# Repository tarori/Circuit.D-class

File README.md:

Class D amplifier using TPA3118

Not recommended because the sound is not so good

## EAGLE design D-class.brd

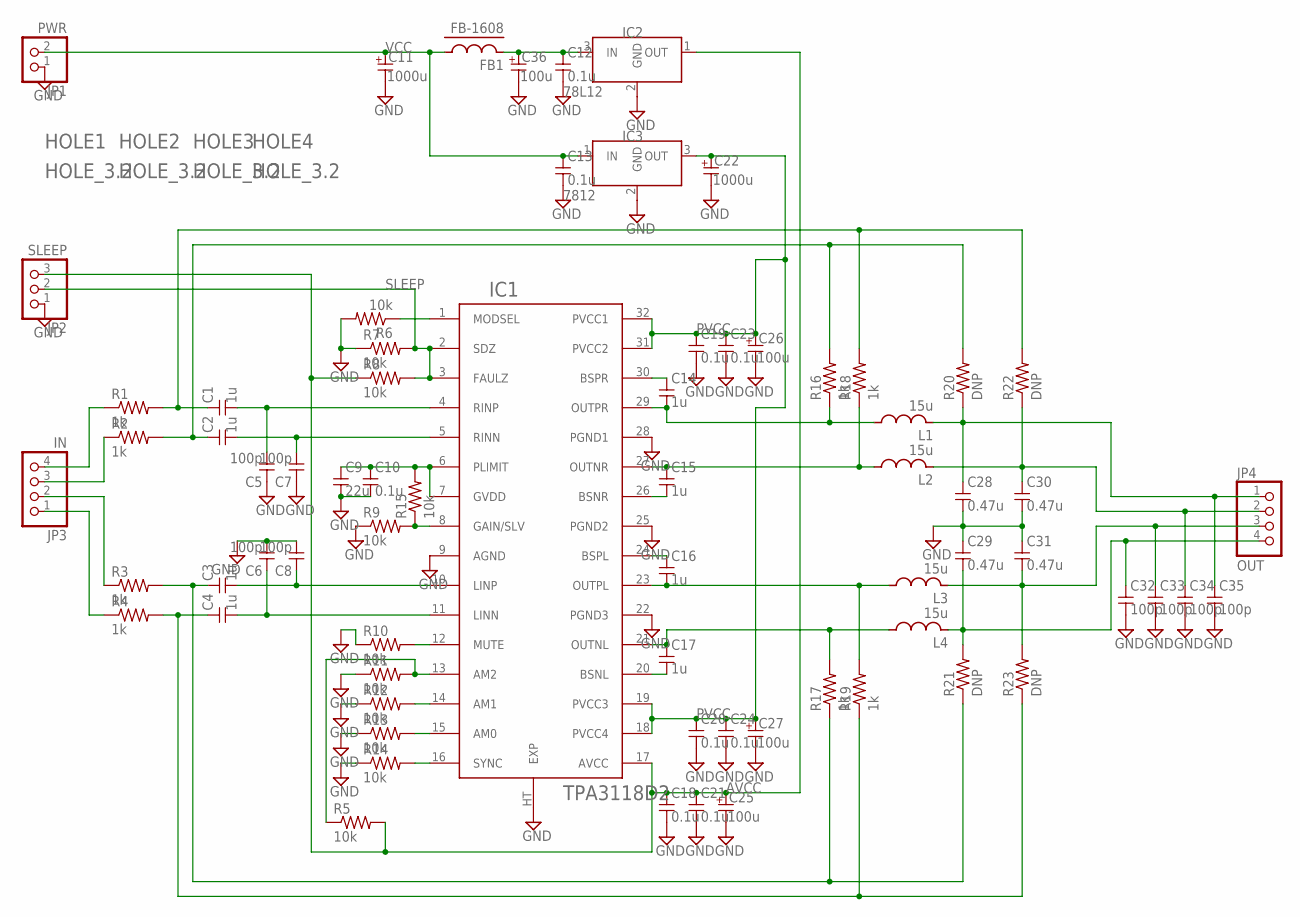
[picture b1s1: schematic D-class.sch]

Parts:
C1, C2, C3, C4: 1u; 3216
C5, C6, C7, C8, C32, C33, C34, C35: 100p; 1608
C9: 22u; 2012
C10, C12, C13, C18, C19, C20: 0.1u; 1608
C11, C22: 1000u; E5-10
C14, C15, C16, C17: 1u; 1608
C21, C23, C24: 0.1u; 2012
C25, C26, C27, C36: 100u; E2.5-6.5
C28, C29, C30, C31: 0.47u; C050-030X075
FB1: FB-1608; 1608
HOLE1, HOLE2, HOLE3, HOLE4: HOLE_3.2
IC1: TPA3118D2; HTSSOP32DAP
IC2: 78L12; TO-92
IC3: 7812; TO-220
JP1: PWR; 1X02
JP2: SLEEP; 1X03
JP3: IN; 1X04
JP4: OUT; 1X04
L1, L2, L3, L4: 15u; L5-7,5
R1, R2, R3, R4, R16, R17, R18, R19: 1k; 0207/2V
R5, R6, R7, R8, R9, R10, R11, R12, R13, R14, R15: 10k; 1608
R20, R21, R22, R23: DNP; 0207/2V

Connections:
AVCC: C18.1, C21.1, C25.+ (1), IC1.17 (AVCC), IC2.1 (OUT), JP2.3, R5.2, R8.1
GND: C5.1, C6.2, C7.1, C8.2, C9.2, C10.2, C11.- (2), C12.2, C13.2, C18.2, C19.2, C20.2, C21.2, C22.- (2), C23.2, C24.2, C25.- (2), C26.- (2), C27.- (2), C28.2, C29.1, C30.2, C31.1, C32.2, C33.2, C34.2, C35.2, C36.- (2), IC1.9 (AGND), IC1.22 (PGND3), IC1.25 (PGND2), IC1.28 (PGND1), IC1.HT (EXP), IC2.2 (GND), IC3.2 (GND), JP1.1, JP2.1, R6.2, R7.1, R9.1, R10.1, R11.1, R12.1, R13.1, R14.1
unnamed: C2.2, C7.2, IC1.5 (RINN)
unnamed: IC1.13 (AM2), R5.1, R11.2
unnamed: IC1.14 (AM1), R12.2
unnamed: IC1.15 (AM0), R13.2
unnamed: IC1.16 (SYNC), R14.2
unnamed: C12.1, C36.+ (1), FB1.2, IC2.3 (IN)
unnamed: C17.2, IC1.20 (BSNL)
unnamed: C17.1, IC1.21 (OUTNL), L4.P$1 (1), R17.2
unnamed: C16.2, IC1.23 (OUTPL), L3.P$1 (1), R19.2
unnamed: C16.1, IC1.24 (BSPL)
unnamed: C15.2, IC1.26 (BSNR)
unnamed: C15.1, IC1.27 (OUTNR), L2.P$1 (1), R18.1
unnamed: C14.2, IC1.29 (OUTPR), L1.P$1 (1), R16.1
unnamed: C14.1, IC1.30 (BSPR)
unnamed: C3.2, C8.1, IC1.10 (LINP)
unnamed: C9.1, C10.1, IC1.6 (PLIMIT), IC1.7 (GVDD), R15.2
unnamed: IC1.8 (GAIN/SLV), R9.2, R15.1
unnamed: C3.1, R3.2, R17.1, R21.1
unnamed: C4.1, R4.2, R19.1, R23.1
unnamed: C1.1, R1.2, R18.2, R22.2
unnamed: C2.1, R2.2, R16.2, R20.2
unnamed: C31.2, C33.1, JP4.3, L3.P$2 (2), R23.2
unnamed: C29.2, C32.1, JP4.4, L4.P$2 (2), R21.2
unnamed: C30.1, C34.1, JP4.2, L2.P$2 (2), R22.1
unnamed: C28.1, C35.1, JP4.1, L1.P$2 (2), R20.1
unnamed: JP3.2, R3.1
unnamed: JP3.1, R4.1
unnamed: JP3.3, R2.1
unnamed: JP3.4, R1.1
unnamed: IC1.1 (MODSEL), R6.1
unnamed: IC1.12 (MUTE), R10.2
unnamed: C1.2, C5.2, IC1.4 (RINP)
unnamed: C4.2, C6.1, IC1.11 (LINN)
PVCC: C19.1, C20.1, C22.+ (1), C23.1, C24.1, C26.+ (1), C27.+ (1), IC1.18 (PVCC4), IC1.19 (PVCC3), IC1.31 (PVCC2), IC1.32 (PVCC1), IC3.3 (OUT)
SLEEP: IC1.2 (SDZ), IC1.3 (FAULZ), JP2.2, R7.2, R8.2
VCC: C11.+ (1), C13.1, FB1.1, IC3.1 (IN), JP1.2

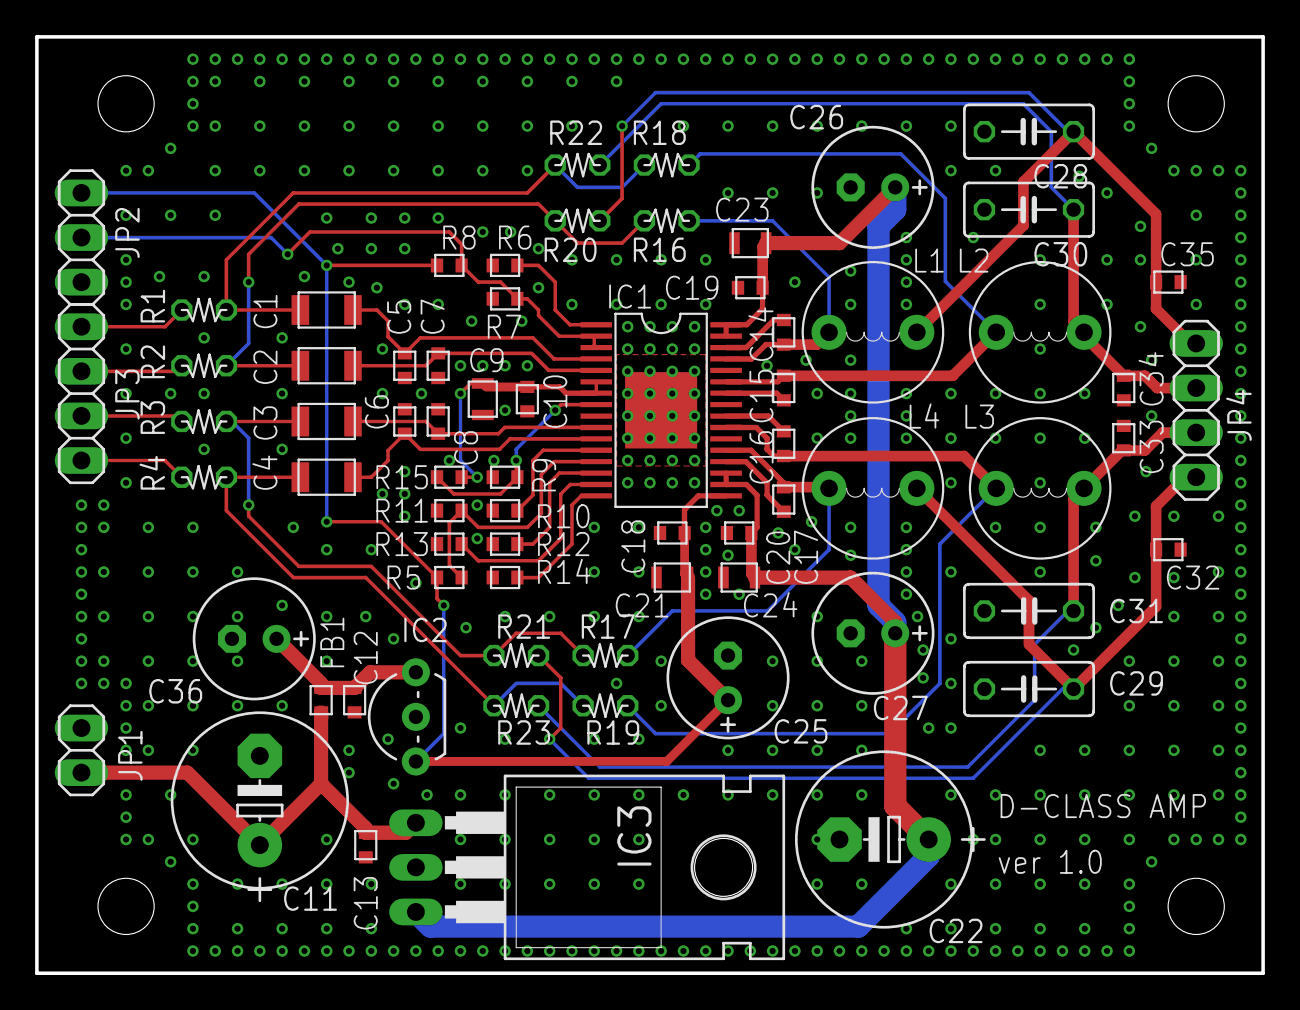
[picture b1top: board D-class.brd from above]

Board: 2 copper layers, 69.8 x 53.3 mm, 75 parts (0 on the bottom side), 38 nets.

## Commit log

2020-02-06 回路図できた
2020-02-06 後はGNDのみ
2020-02-07 後はシルクのみ
2020-07-03 Add readme
